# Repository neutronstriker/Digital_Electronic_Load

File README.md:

# Digital_Electronic_Load
An Electronic Load based on Arduino and some analog components
Components used are:
Arduino Nano-1
OLED I2C display 0.96Inch - 1
TPL0102-100PWR I2C DIGITAL PORT -1
LM358  DUAL OPAMP -1
INA226 Shunt Current / Power sensor - 1
2N3055 - NPN Power transistor -1
1 OHM / 10W resistor -1

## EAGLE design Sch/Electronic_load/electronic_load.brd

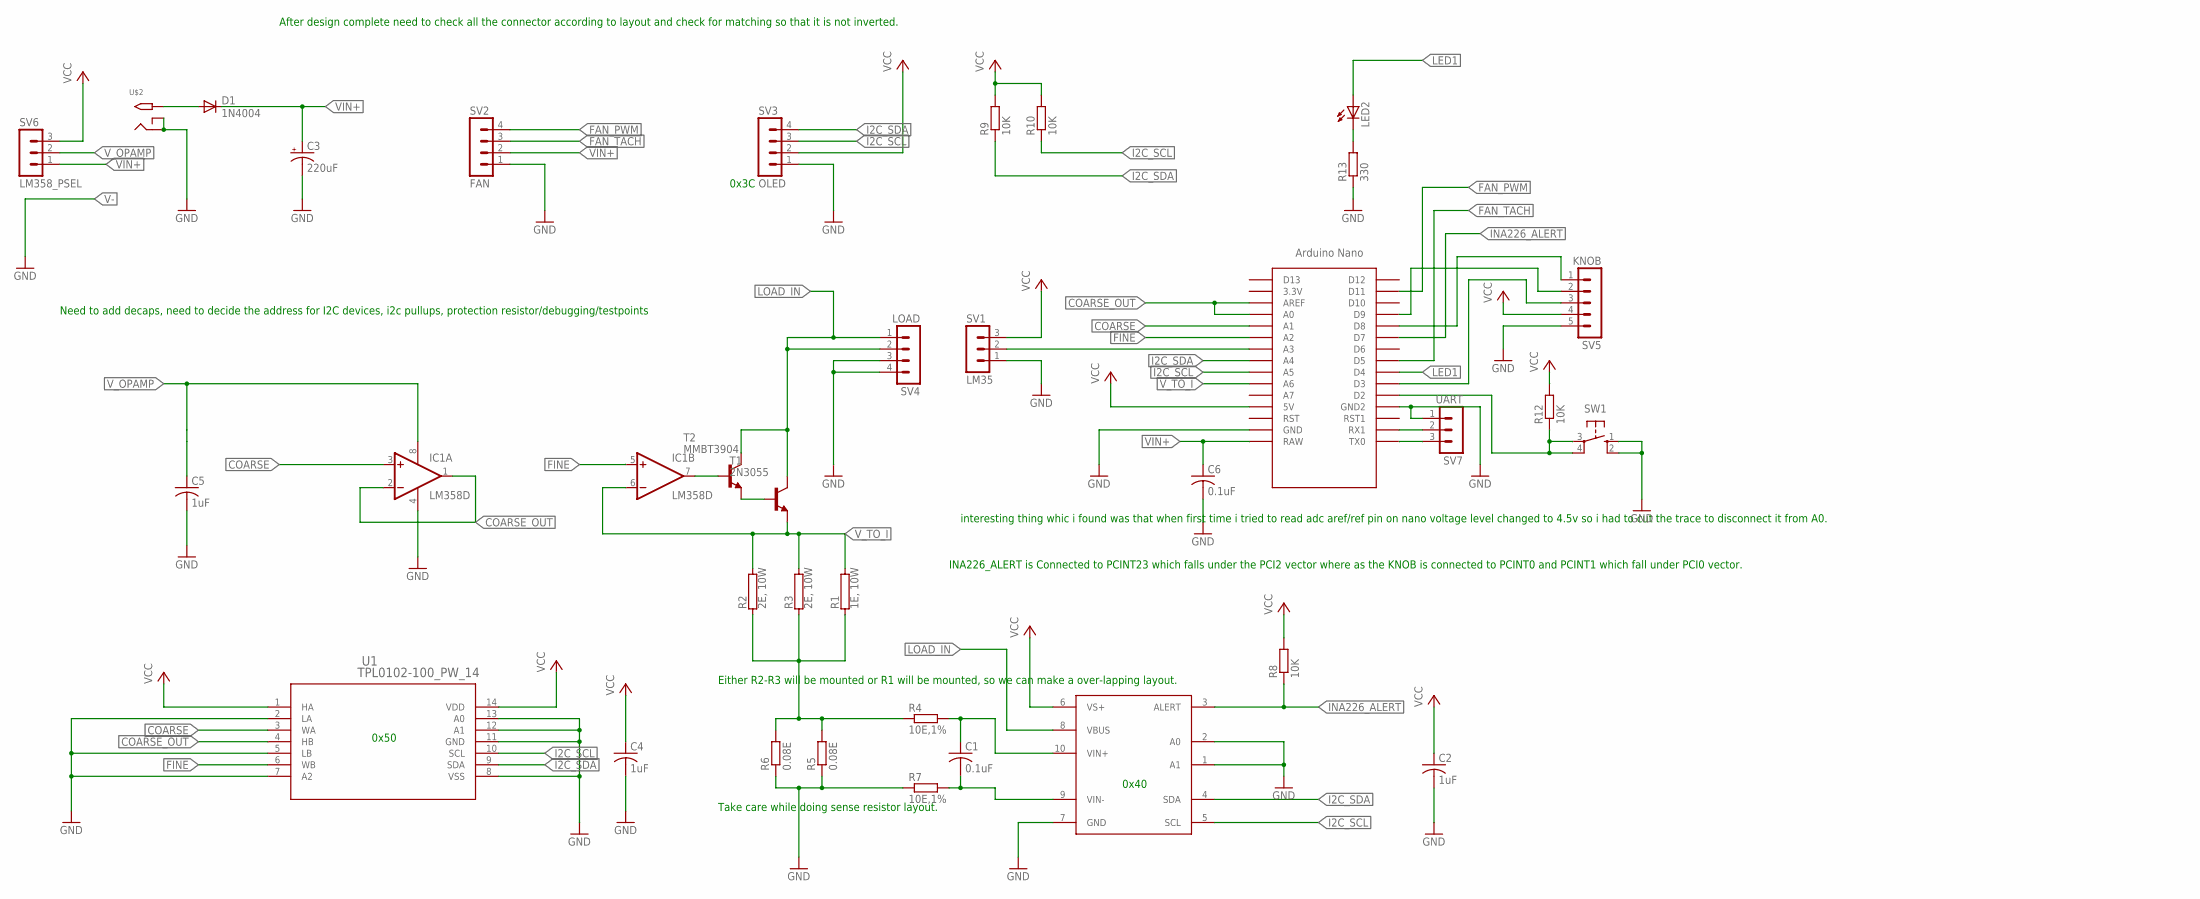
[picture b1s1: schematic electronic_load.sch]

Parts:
C1: 0.1uF; C0805
C2, C4: 1uF; C0805
C3: 220uF; E3,5-8
C5: 1uF; C1206
C6: 0.1uF; C1206
D1: 1N4004; DO41-10
IC1: LM358D; SO08
LED2: LED3MM
R1: 1E, 10W; AC10
R2, R3: 2E, 10W; CA4150
R4, R7: 10E,1%; R0805
R5, R6: 0.08E; R2512
R8, R9, R10, R12: 10K; R0805
R13: 330; R0805
SV1: LM35; MA03-1
SV2: FAN; MA04-1
SV3: OLED; MA04-1
SV4: LOAD; MA04-1
SV5: KNOB; MA05-1
SV6: LM358_PSEL; MA03-1
SV7: UART; MA03-1
SW1: 10-XX; B3F-10XX
T1: 2N3055; TO3
T2: MMBT3904; SOT23-BEC
U1: TPL0102-100_PW_14; PW14
U2: INA226AIDGST; SOP50P490X110-10N
U$1: NANO
U$2: 2.1MMJACKTHM; PJ-102A

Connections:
COARSE: IC1.3 (+IN), U1.3 (WA), U$1.A1
COARSE_OUT: IC1.1 (OUT), IC1.2 (-IN), U1.4 (HB), U$1.A0, U$1.AREF
FAN_PWM: SV2.4, U$1.D11
FAN_TACH: SV2.3, U$1.D5
FINE: IC1.5 (+IN), U1.6 (WB), U$1.A2
GND: C2.2, C3.-, C4.2, C5.2, C6.2, IC1.4 (V-), R5.1, R6.1, R7.1, R13.1, SV1.1, SV2.1, SV3.1, SV4.3, SV4.4, SV5.5, SV7.1, SW1.1 (S), SW1.2 (S1), U1.2 (LA), U1.5 (LB), U1.7 (A2), U1.8 (VSS), U1.11 (GND), U1.12 (A1), U1.13 (A0), U2.1 (A1), U2.2 (A0), U2.7 (GND), U$1.GND, U$1.GND1 (GND2), U$2.RING, U$2.RING_SW
I2C_SCL: R10.1, SV3.3, U1.10 (SCL), U2.5 (SCL), U$1.A5
I2C_SDA: R9.1, SV3.4, U1.9 (SDA), U2.4 (SDA), U$1.A4
INA226_ALERT: R8.1, U2.3 (ALERT), U$1.D7
LED1: LED2.A, U$1.D4
LOAD_IN: SV4.1, SV4.2, T1.C, T1.C/ (C), T2.C, U2.8 (VBUS)
unnamed: SV7.2, U$1.RX1
unnamed: D1.A, U$2.TIP
unnamed: T1.B, T2.E
unnamed: R1.1, R2.1, R3.1, R4.1, R5.2, R6.2
unnamed: C1.1, R4.2, U2.10 (VIN+)
unnamed: SV1.2, U$1.A3
unnamed: C1.2, R7.2, U2.9 (VIN-)
unnamed: IC1.7 (OUT), T2.B
unnamed: SV5.3, U$1.D3
unnamed: R12.1, SW1.3, SW1.4 (P1), U$1.D2
unnamed: LED2.K (C), R13.2
unnamed: SV7.3, U$1.TX0
unnamed: SV5.2, U$1.D9
unnamed: SV5.1, U$1.D8
VCC: C2.1, C4.1, R8.2, R9.2, R10.2, R12.2, SV1.3, SV3.2, SV5.4, SV6.3, U1.1 (HA), U1.14 (VDD), U2.6 (VS+), U$1.5V
VIN+: C3.+, C6.1, D1.C, SV2.2, SV6.1, U$1.RAW
V_OPAMP: C5.1, IC1.8 (V+), SV6.2
V_TO_I: IC1.6 (-IN), R1.2, R2.2, R3.2, T1.E, U$1.A6

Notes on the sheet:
Need to add decaps, need to decide the address for I2C devices, i2c pullups, protection resistor/debugging/testpoints
Either R2-R3 will be mounted or R1 will be mounted, so we can make a over-lapping layout.
Take care while doing sense resistor layout.
After design complete need to check all the connector according to layout and check for matching so that it is not inverted.
0x50
0x40
0x3C
INA226_ALERT is Connected to PCINT23 which falls under the PCI2 vector where as the KNOB is connected to PCINT0 and PCINT1 which fall under PCI0 vector.
interesting thing whic i found was that when first time i tried to read adc aref/ref pin on nano voltage level changed to 4.5v so i had to cut the trace to disconnect it from A0.

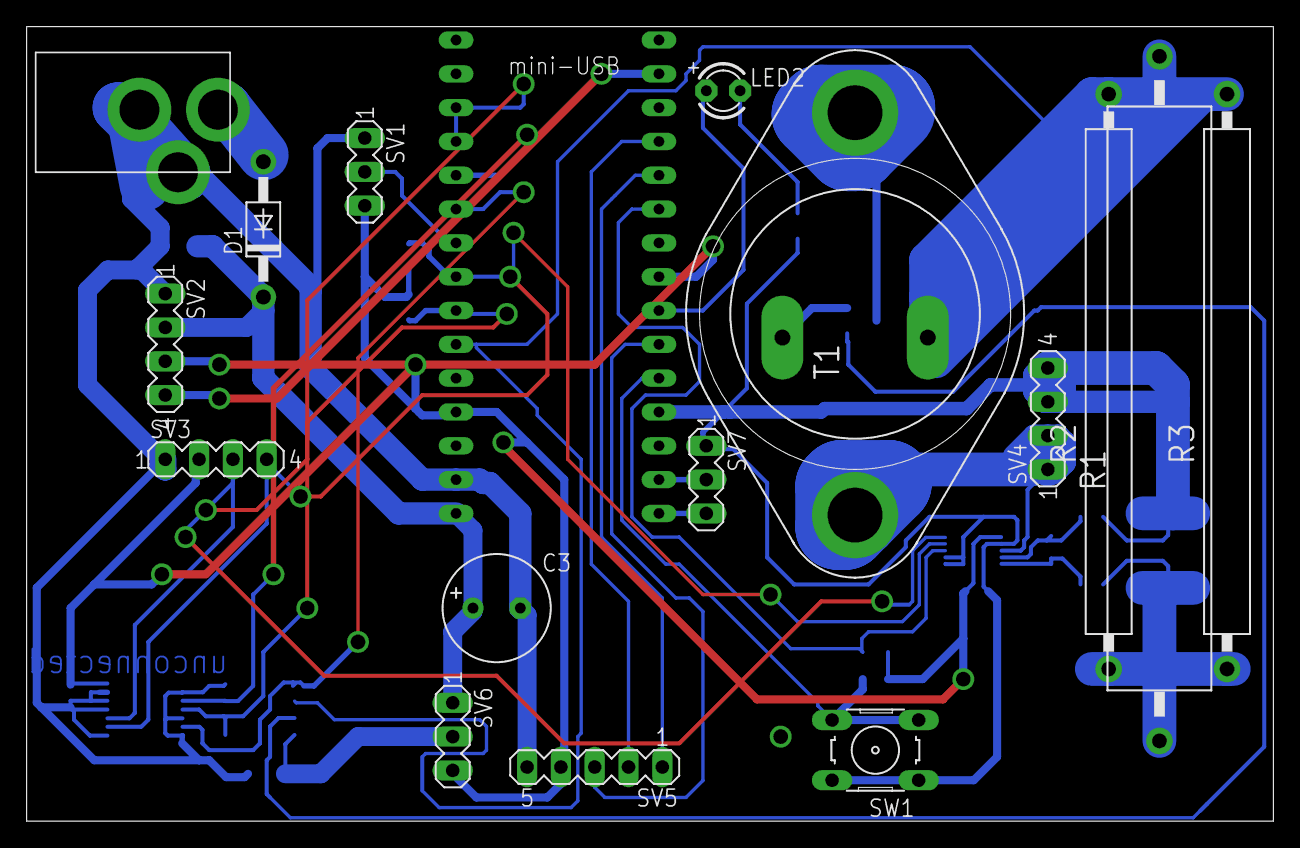
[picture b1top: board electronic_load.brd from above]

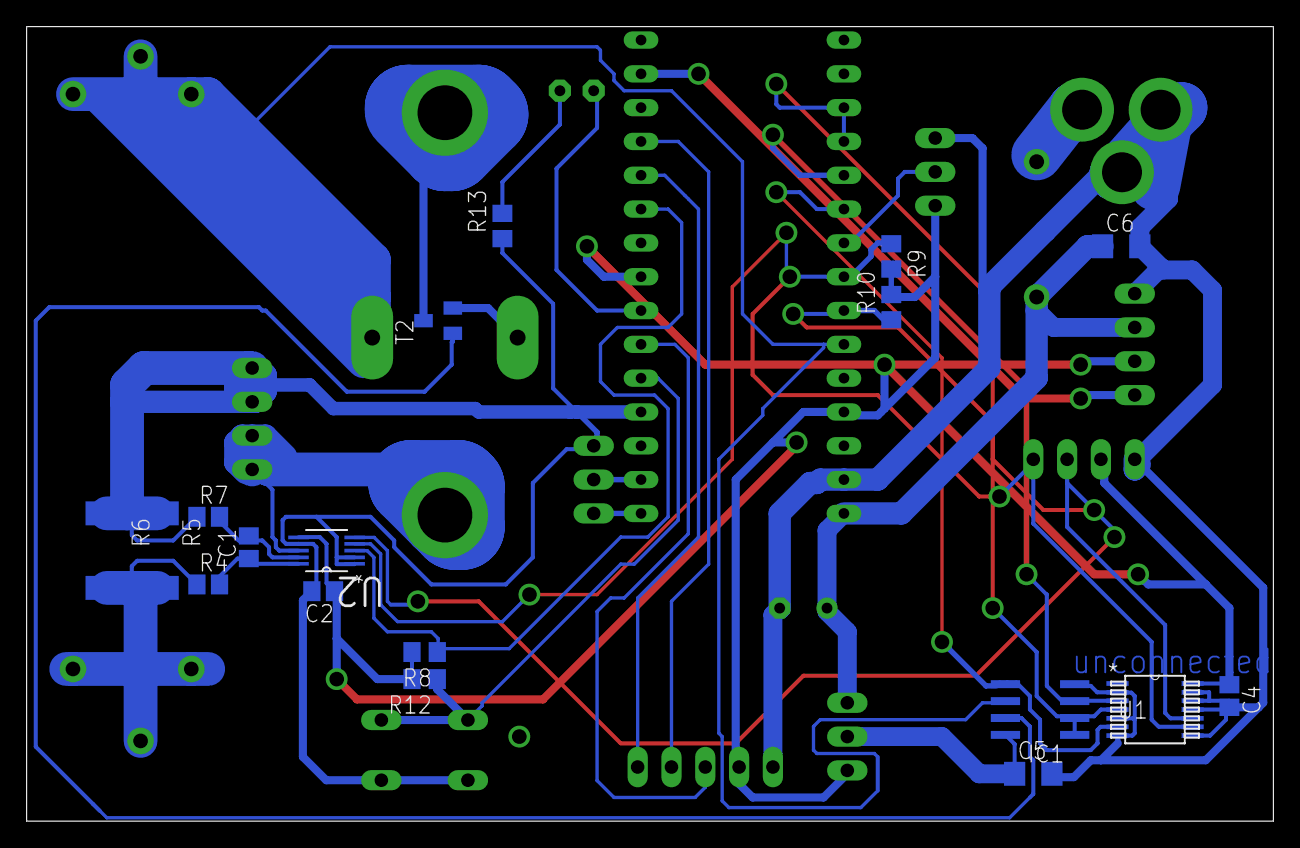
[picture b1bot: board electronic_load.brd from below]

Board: 2 copper layers, 93.7 x 59.7 mm, 35 parts (18 on the bottom side), 29 nets.

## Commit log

2018-10-30 uploaded code
2018-11-14 added temp?, tset and help commands
2018-11-14 bug fix
